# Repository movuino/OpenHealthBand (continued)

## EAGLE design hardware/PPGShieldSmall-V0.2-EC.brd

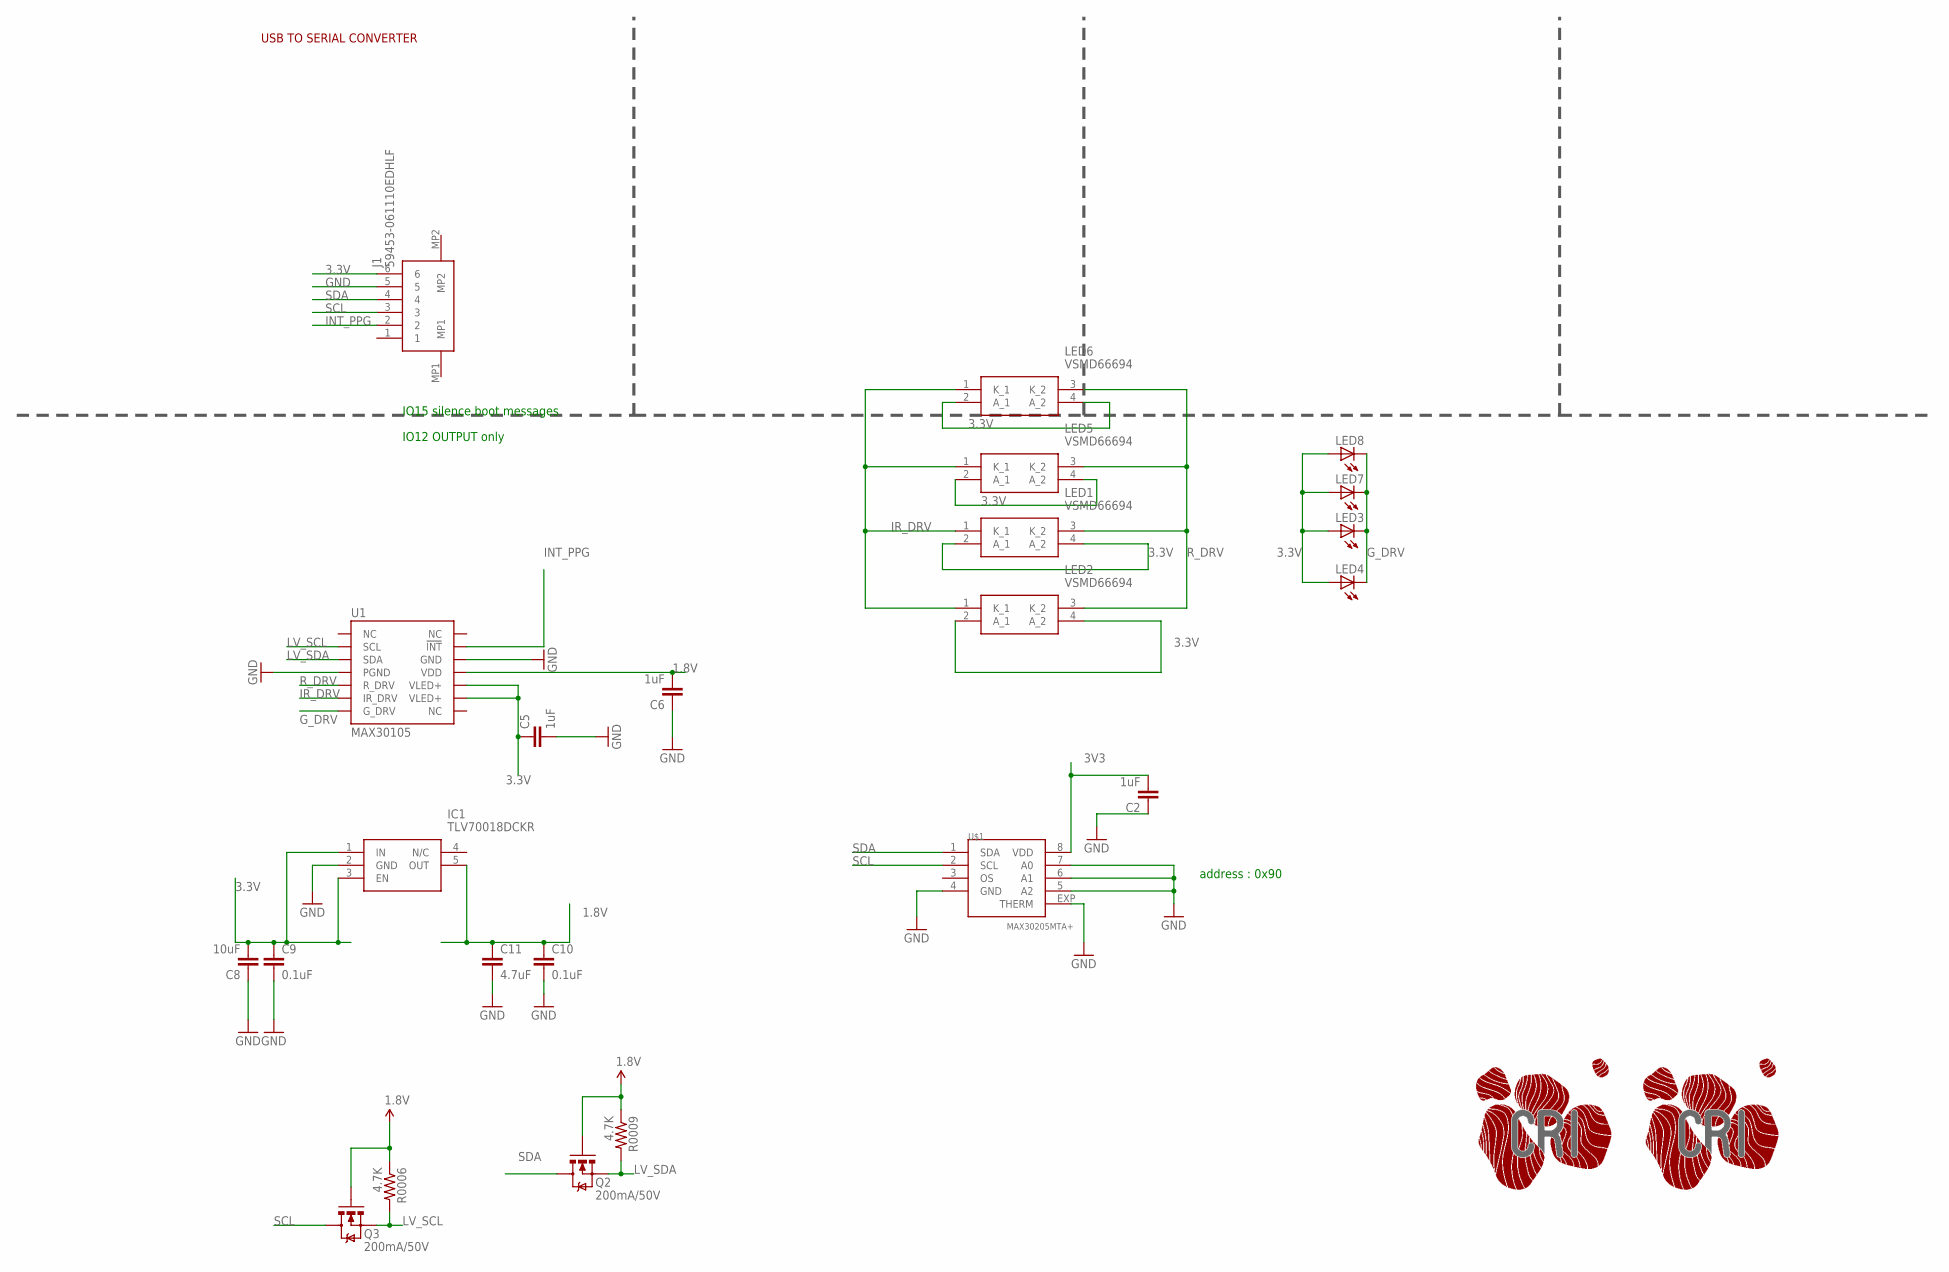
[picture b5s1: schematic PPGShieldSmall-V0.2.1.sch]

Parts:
C2, C5, C6: 1uF; 0402-CAP
C8: 10uF; 0402-RES
C9, C10: 0.1uF; 0402-CAP
C11: 4.7uF; 0402-CAP
IC1: TLV70018DCKR; SOT65P210X110-5N
J1: 59453-061110EDHLF; 59453061110EDHLF
LED1, LED2, LED5, LED6: VSMD66694
LED3, LED4, LED7, LED8: LED0603; LED-0603
Q2, Q3: 200mA/50V; SOT23-3
R0006, R0009: 4.7K; 0402-RES
U1: MAX30105; OLGA-14
U$1: MAX30205MTA+; TDFN-08
U$3, U$4: LOGO-CRI-NEW-110MM-BOTTOM-SILK; LOGO_CRI-NEW-BMP10MM-BOTTOM

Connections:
1.8V: C6.2, C10.1, C11.1, IC1.5 (OUT), Q2.1 (G), Q3.1 (G), R0006.1, R0009.1, U1.11 (VDD)
3.3V: C5.1, C8.2, C9.1, IC1.1 (IN), IC1.3 (EN), J1.6, LED1.2 (A_1), LED1.4 (A_2), LED2.2 (A_1), LED2.4 (A_2), LED3.A, LED4.A, LED5.2 (A_1), LED5.4 (A_2), LED6.2 (A_1), LED6.4 (A_2), LED7.A, LED8.A, U1.9 (VLED+), U1.10 (VLED+)
3V3: C2.2, U$1.8 (VDD)
GND: C2.1, C5.2, C6.1, C8.1, C9.2, C10.2, C11.2, IC1.2 (GND), J1.5, U1.4 (PGND), U1.12 (GND), U$1.4 (GND), U$1.5 (A2), U$1.6 (A1), U$1.7 (A0), U$1.EXP (THERM)
G_DRV: LED3.C, LED4.C, LED7.C, LED8.C, U1.7 (G_DRV)
INT_PPG: J1.2, U1.13 (!INT)
IR_DRV: LED1.1 (K_1), LED2.1 (K_1), LED5.1 (K_1), LED6.1 (K_1), U1.6 (IR_DRV)
LV_SCL: Q3.2 (S), R0006.2, U1.2 (SCL)
LV_SDA: Q2.2 (S), R0009.2, U1.3 (SDA)
R_DRV: LED1.3 (K_2), LED2.3 (K_2), LED5.3 (K_2), LED6.3 (K_2), U1.5 (R_DRV)
SCL: J1.3, Q3.3 (D), U$1.2 (SCL)
SDA: J1.4, Q2.3 (D), U$1.1 (SDA)

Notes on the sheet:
USB TO SERIAL CONVERTER
IO12 OUTPUT only
IO15 silence boot messages
address : 0x90

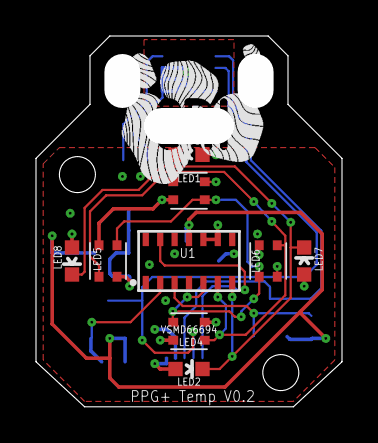
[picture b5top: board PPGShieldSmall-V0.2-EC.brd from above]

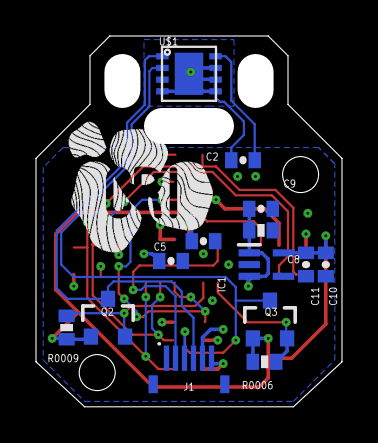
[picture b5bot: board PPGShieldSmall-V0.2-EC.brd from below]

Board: 4 copper layers, 17.0 x 20.6 mm, 25 parts (15 on the bottom side), 12 nets.

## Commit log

2020-01-20 Code for BLE characteristics
    Code for Device Information, Battery Level, Heart Rate Measurement and Health Thermometer
2020-03-24 added pcb files
2020-03-24 added BLE doc
2021-08-28 added shield PPG MAX86141 v0.2.1 (BSS138 level shifter)
2021-08-28 added v0.2.2 (level convertion IC)
2021-08-28 added carrier USB Dev board
2021-08-31 update board
2022-05-10 Documented licence to comply with pidcodes project guidelines
